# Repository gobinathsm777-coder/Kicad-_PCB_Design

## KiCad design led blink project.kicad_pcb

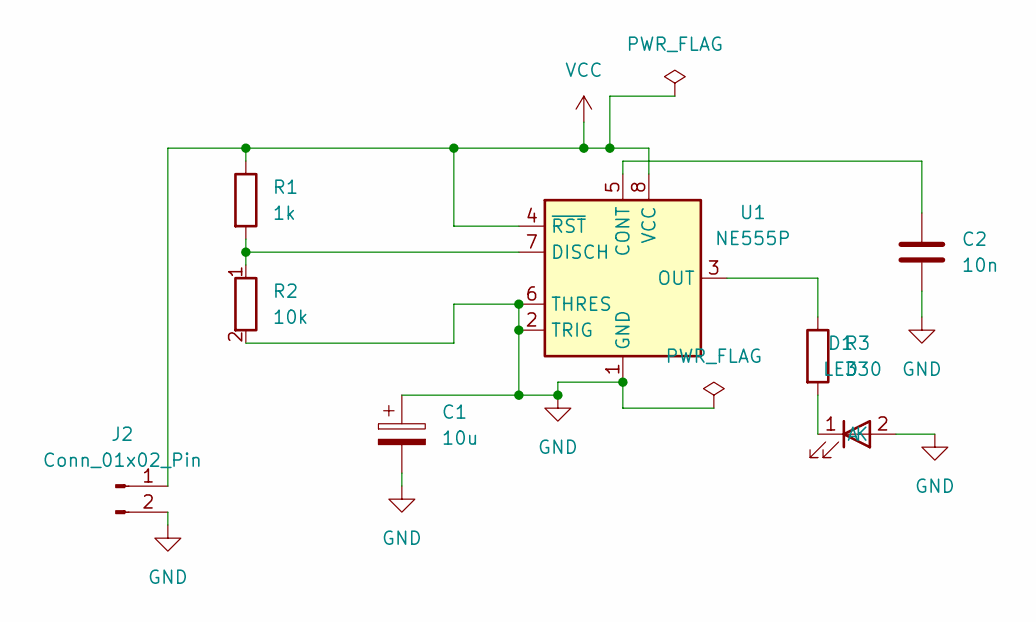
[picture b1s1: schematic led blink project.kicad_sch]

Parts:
C1: 10u; CP_Radial_D5.0mm_P2.00mm
C2: 10n; C_Disc_D3.8mm_W2.6mm_P2.50mm
D1: LED; LED_D5.0mm
J2: Conn_01x02_Pin; PinHeader_1x02_P2.54mm_Vertical
R1: 1k; R_Axial_DIN0207_L6.3mm_D2.5mm_P7.62mm_Horizontal
R2: 10k; R_Axial_DIN0207_L6.3mm_D2.5mm_P7.62mm_Horizontal
R3: 330; R_Axial_DIN0207_L6.3mm_D2.5mm_P7.62mm_Horizontal
U1: NE555P; DIP-8_W7.62mm

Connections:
GND: C1.1, C1.2, C2.2, D1.2 (A), J2.2, R2.2, U1.1 (GND), U1.2 (TRIG), U1.6 (THRES)
unnamed: D1.1 (K), R3.2
unnamed: C2.1, U1.5 (CONT)
unnamed: R1.2, R2.1, U1.7 (DISCH)
unnamed: R3.1, U1.3 (OUT)
VCC: J2.1, R1.1, U1.4 (~RST), U1.8 (VCC)

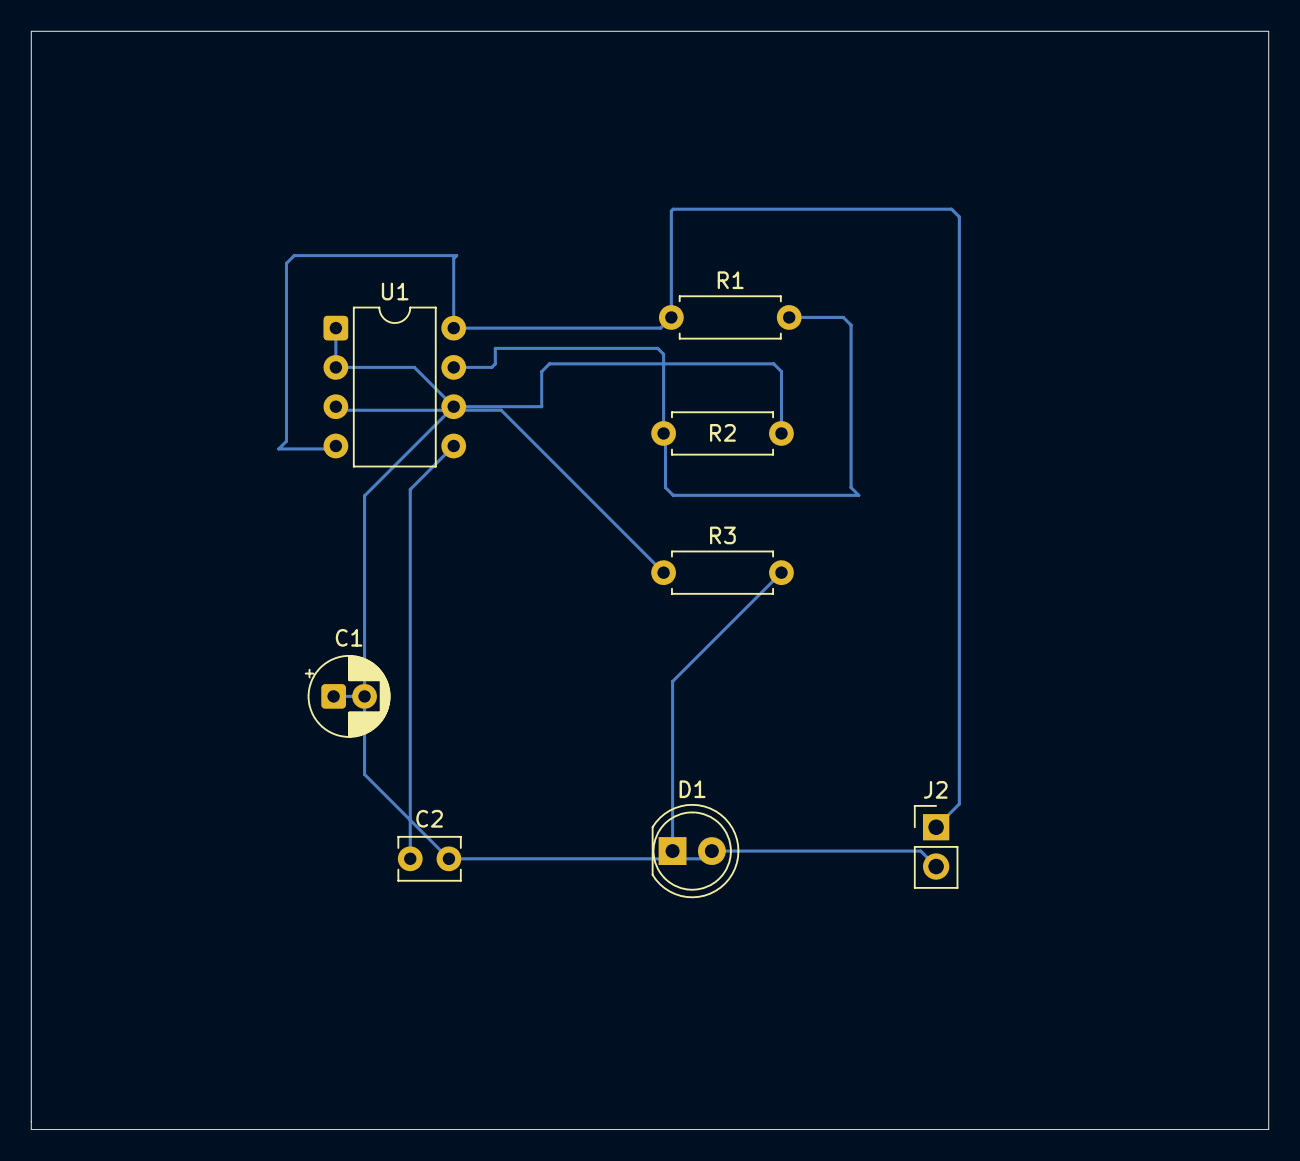
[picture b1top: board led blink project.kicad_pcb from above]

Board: 2 copper layers, 80.0 x 71.0 mm, 8 parts (0 on the bottom side), 6 nets.
